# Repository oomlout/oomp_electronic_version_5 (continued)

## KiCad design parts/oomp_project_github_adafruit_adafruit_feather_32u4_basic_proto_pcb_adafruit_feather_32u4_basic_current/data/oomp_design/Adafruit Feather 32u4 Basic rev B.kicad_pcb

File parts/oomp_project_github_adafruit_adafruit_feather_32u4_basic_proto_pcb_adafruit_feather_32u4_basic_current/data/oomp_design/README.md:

# OOMP KiCad design copy

Open `Adafruit Feather 32u4 Basic rev B.kicad_pro` (or the `.kicad_pcb` / `.kicad_sch`) in KiCad. Local OOMP libraries are under `libraries/`. Original inputs are preserved in [../original/](../original/).

Only verified unchanged installed KiCad defaults were renamed. Modified, custom, unmatched and unavailable items remain unchanged. Soldering variants are never swapped during conversion. Existing pad coordinates, nets and UUIDs are preserved.

See [conversion_report.yaml](conversion_report.yaml) for every conversion and skip. Copy this directory before editing; regeneration refuses to overwrite edited design files.

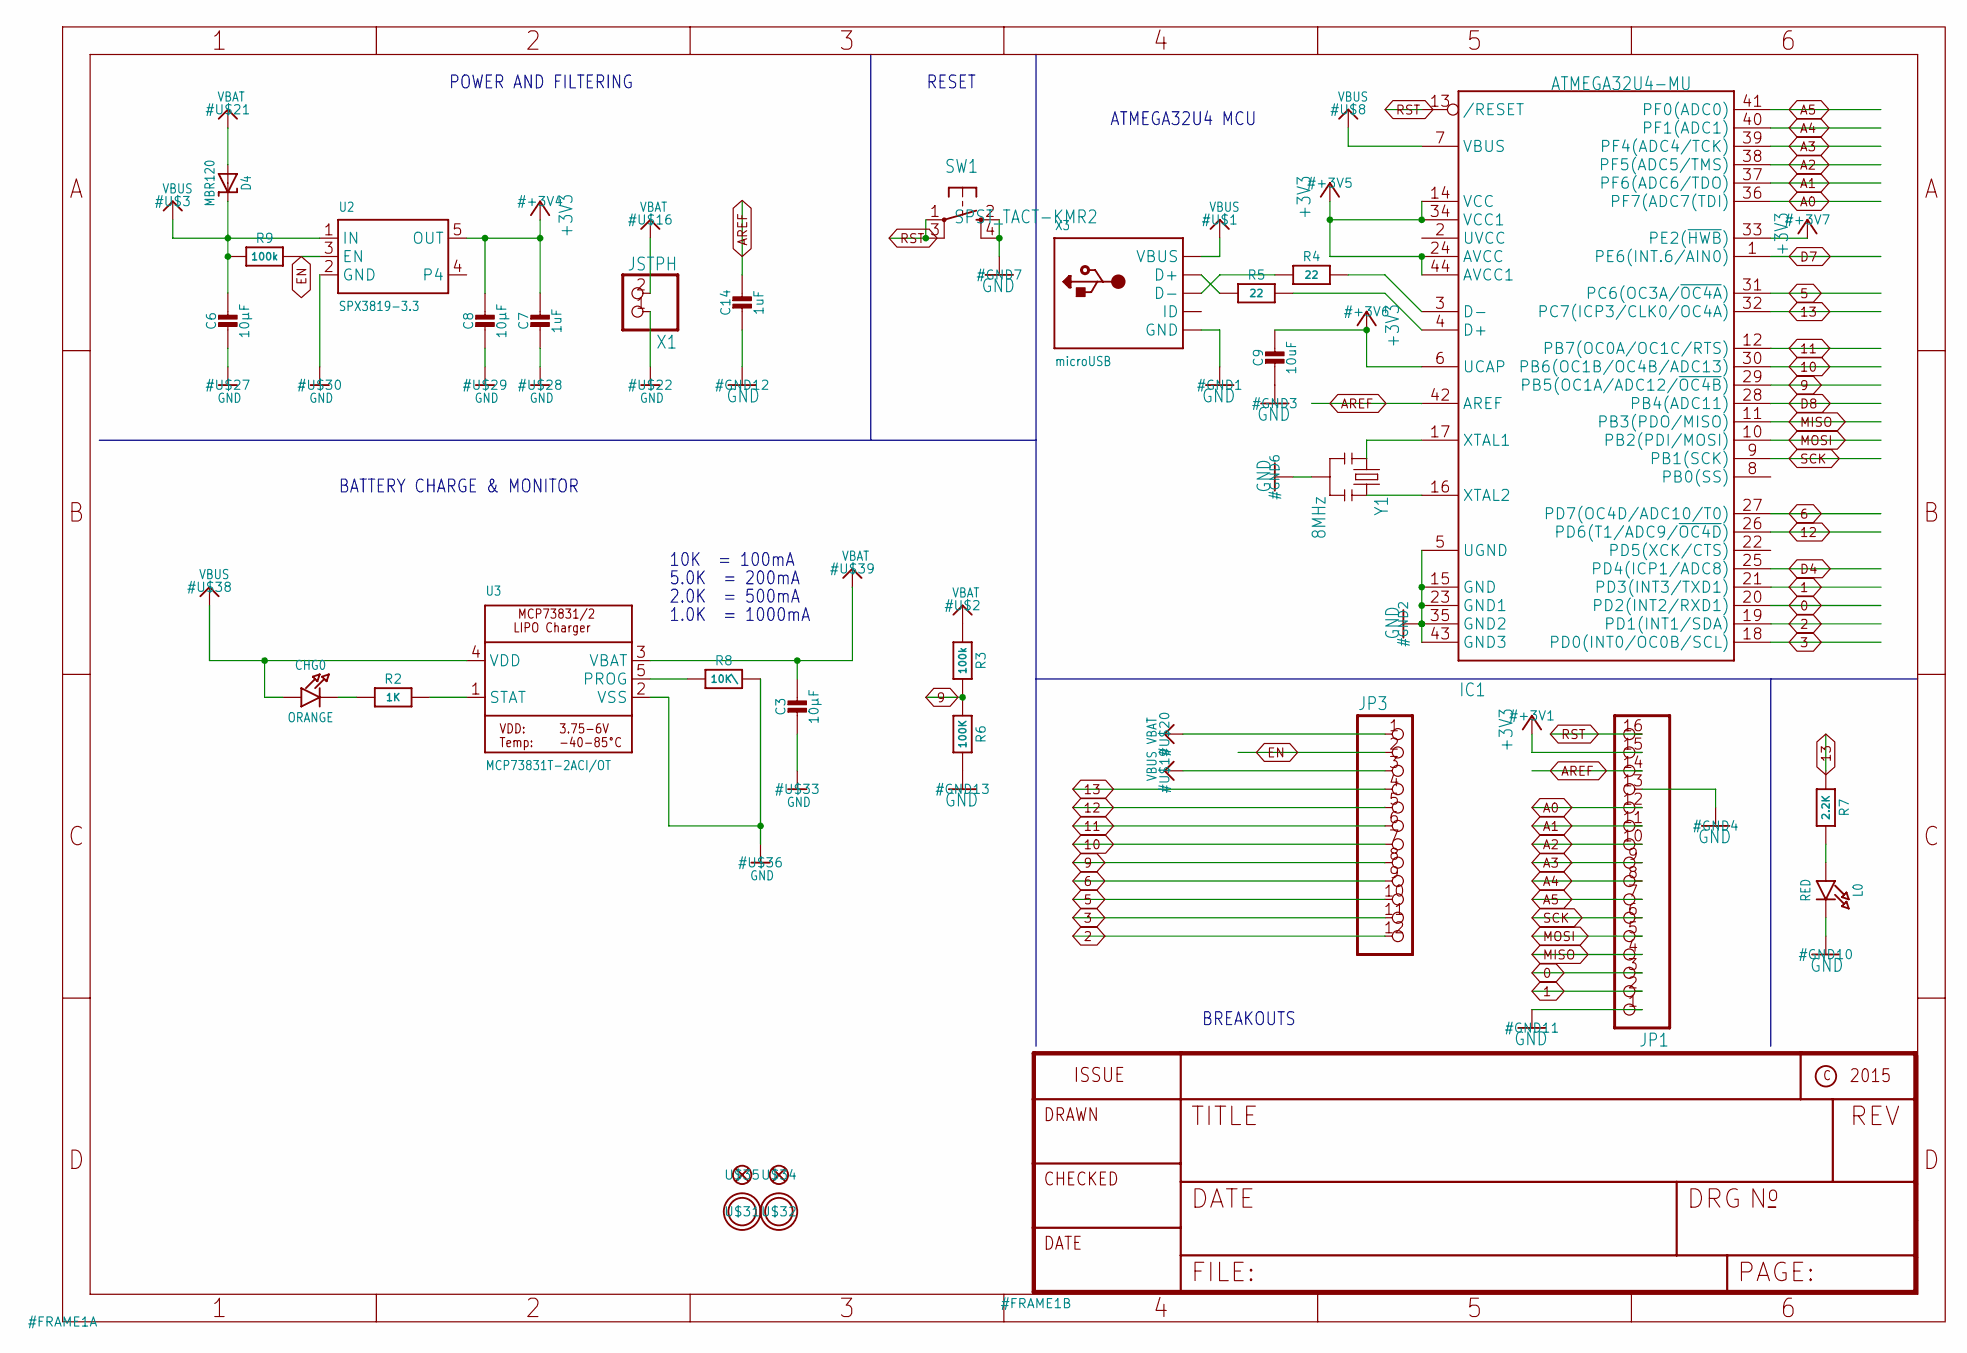
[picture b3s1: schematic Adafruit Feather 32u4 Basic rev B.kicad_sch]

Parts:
C3, C6, C8: 10µF; 0805-NO
C7, C14: 1uF; 0603-NO
C9: 10uF; 0805-NO
CHG0: ORANGE; CHIPLED_0805_NOOUTLINE
D4: MBR120; SOD-123
IC1: ATMEGA32U4-MU; TQFN44_7MM
JP1: HEADER-1X16ROUND; 1X16_ROUND
JP3: HEADER-1X12; 1X12_ROUND
L0: RED; CHIPLED_0805_NOOUTLINE
R2: 1K; 0603-NO
R3, R9: 100k; 0603-NO
R4, R5: 22; 0603-NO
R6: 100K; _0603MP
R7: 2.2K; 0603-NO
R8: 10K\; 0603-NO
SW1: SPST_TACT-KMR2; KMR2
U2: SPX3819-3.3; SOT23-5
U3: MCP73831T-2ACI/OT; SOT23-5
U$31, U$32: MOUNTINGHOLE2.5; MOUNTINGHOLE_2.5_PLATED
U$34, U$35: FIDUCIAL""; FIDUCIAL_1MM
X1: JSTPH; JSTPH2
X3: microUSB; 4UCONN_20329_V2
Y1: 8MHz; RESONATOR-SMD

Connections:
0: IC1.20 (PD2(INT2/RXD1)), JP1.3
1: IC1.21 (PD3(INT3/TXD1)), JP1.2
2: IC1.19 (PD1(INT1/SDA)), JP3.12
3: IC1.18 (PD0(INT0/OC0B/SCL)), JP3.11
5: IC1.31 (PC6(OC3A/~OC4A)), JP3.10
6: IC1.27 (PD7(OC4D/ADC10/T0)), JP3.9
9: IC1.29 (PB5(OC1A/ADC12/~OC4B)), JP3.8, R3.2, R6.1
10: IC1.30 (PB6(OC1B/OC4B/ADC13)), JP3.7
11: IC1.12 (PB7(OC0A/OC1C/RTS)), JP3.6
12: IC1.26 (PD6(T1/ADC9/~OC4D)), JP3.5
13: IC1.32 (PC7(ICP3/CLK0/OC4A)), JP3.4, R7.1
+3V3: C7.1, C8.1, C9.1, IC1.6 (UCAP), IC1.14 (VCC), IC1.24 (AVCC), IC1.33 (PE2(~HWB)), IC1.34 (VCC1), IC1.44 (AVCC1), JP1.15, U2.5 (OUT)
A0: IC1.36 (PF7(ADC7(TDI)), JP1.12
A1: IC1.37 (PF6(ADC6/TDO)), JP1.11
A2: IC1.38 (PF5(ADC5/TMS)), JP1.10
A3: IC1.39 (PF4(ADC4/TCK)), JP1.9
A4: IC1.40 (PF1(ADC1)), JP1.8
A5: IC1.41 (PF0(ADC0)), JP1.7
AREF: C14.1, IC1.42 (AREF), JP1.14
D4: IC1.25 (PD4(ICP1/ADC8))
D7: IC1.1 (PE6(INT.6/AIN0))
D8: IC1.28 (PB4(ADC11))
D+: IC1.4 (D+), R5.2
D-: IC1.3 (D-), R4.2
EN: JP3.2, R9.2, U2.3 (EN)
GND: C3.2, C6.2, C7.2, C8.2, C9.2, C14.2, IC1.5 (UGND), IC1.15 (GND), IC1.23 (GND1), IC1.35 (GND2), IC1.43 (GND3), JP1.1, JP1.13, L0.C, R6.2, R8.2, SW1.2 (S), SW1.4 (S1), U2.2 (GND), U3.2 (VSS), X1.1, X3.BASE@1 (GND), X3.BASE@2 (GND), X3.GND, X3.SPRT@1 (GND), X3.SPRT@2 (GND), X3.SPRT@3 (GND), X3.SPRT@4 (GND), Y1.2
MISO: IC1.11 (PB3(PDO/MISO)), JP1.4
MOSI: IC1.10 (PB2(PDI/MOSI)), JP1.5
unnamed: CHG0.C, R2.1
unnamed: L0.A, R7.2
unnamed: R2.2, U3.1 (STAT)
unnamed: R8.1, U3.5 (PROG)
unnamed: IC1.16 (XTAL2), Y1.3
unnamed: IC1.17 (XTAL1), Y1.1
unnamed: R5.1, X3.D+
unnamed: R4.1, X3.D-
RST: IC1.13 (/RESET), JP1.16, SW1.1, SW1.3 (P1)
SCK: IC1.9 (PB1(SCK)), JP1.6
VBAT: C3.1, D4.A, JP3.1, R3.1, U3.3 (VBAT), X1.2
VBUS: C6.1, CHG0.A, D4.C, IC1.7 (VBUS), JP3.3, R9.1, U2.1 (IN), U3.4 (VDD), X3.VBUS

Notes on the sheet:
POWER AND FILTERING
BATTERY CHARGE & MONITOR
5.0K = 200mA
2.0K = 500mA
RESET
BREAKOUTS
1.0K = 1000mA
10K = 100mA
ATMEGA32U4 MCU

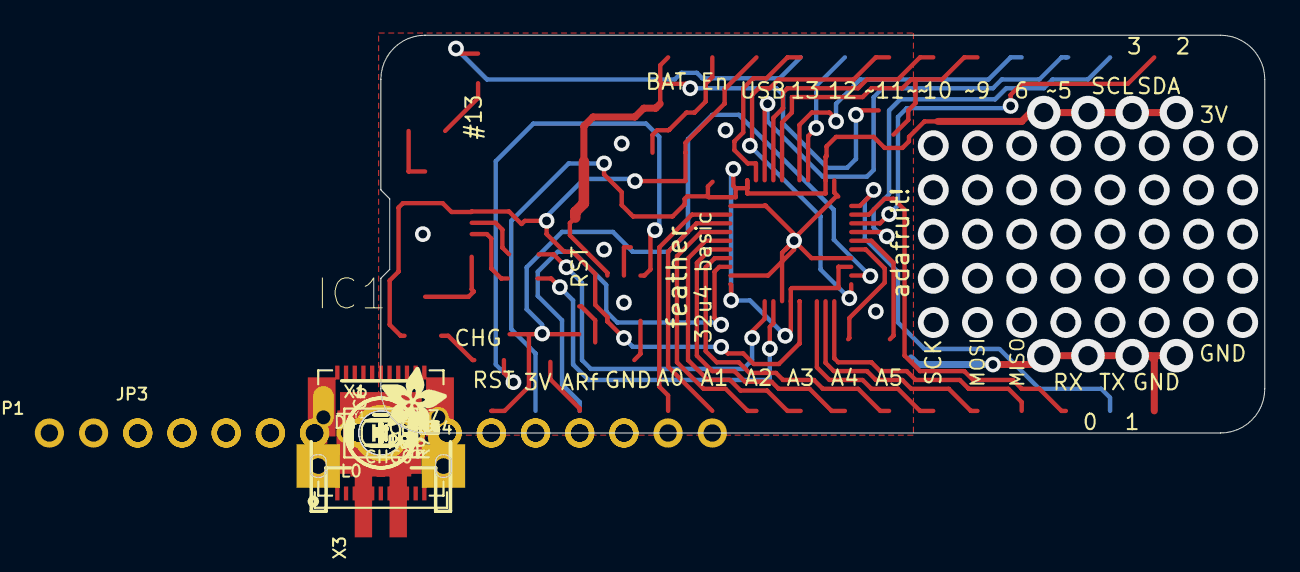
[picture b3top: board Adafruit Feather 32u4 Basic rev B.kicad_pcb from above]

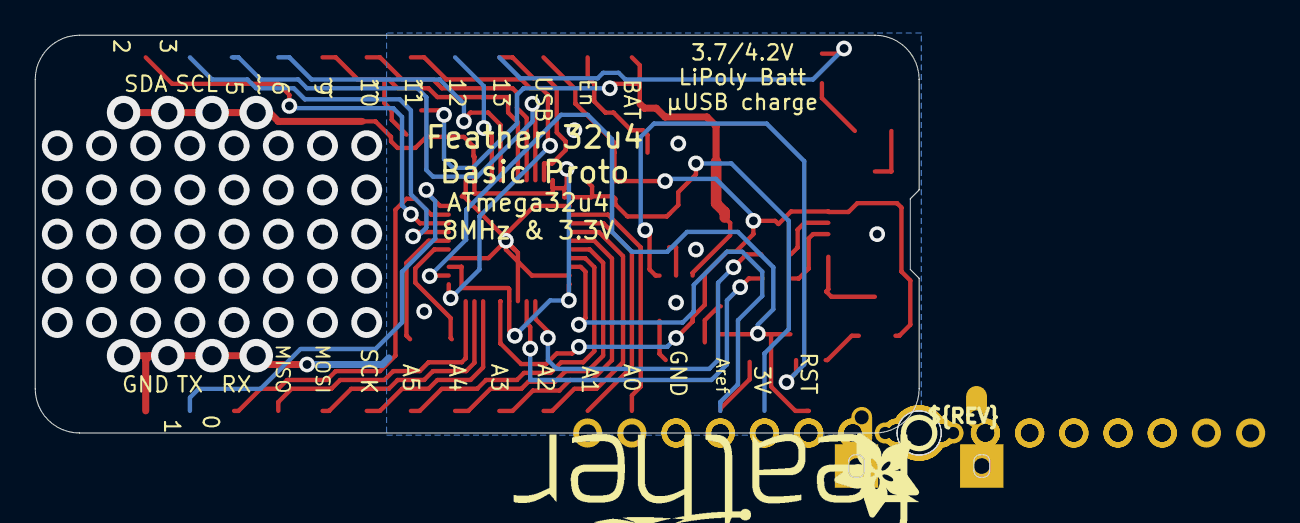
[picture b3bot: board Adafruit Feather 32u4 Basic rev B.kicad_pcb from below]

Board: 2 copper layers, 50.8 x 22.9 mm, 36 parts (3 on the bottom side), 37 nets.

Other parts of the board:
U$4: ADAFRUIT_5MM
U$5: FEATHERLOGO
U$6: PCBFEAT-REV-040
U$7: ADAFRUIT_3.5MM
UNK_HOLE_0: dummyfp0
UNK_HOLE_1: dummyfp1

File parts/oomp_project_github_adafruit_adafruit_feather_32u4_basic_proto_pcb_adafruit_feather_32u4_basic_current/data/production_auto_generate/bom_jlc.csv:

Comment,Designator,Footprint,LCSC Part #
,JP3,Adafruit Feather 32u4 Basic rev B-import-fps:1X12_ROUND,C7501588
,JP1,Adafruit Feather 32u4 Basic rev B-import-fps:1X16_ROUND,C7501270
,U$7,Adafruit Feather 32u4 Basic rev B-import-fps:ADAFRUIT_3.5MM,
,U$4,Adafruit Feather 32u4 Basic rev B-import-fps:ADAFRUIT_5MM,
,U$5,Adafruit Feather 32u4 Basic rev B-import-fps:FEATHERLOGO,
,U$6,Adafruit Feather 32u4 Basic rev B-import-fps:PCBFEAT-REV-040,
100k,"R3,R9",Adafruit Feather 32u4 Basic rev B-import-fps:0603-NO,C25803
100K,R6,Adafruit Feather 32u4 Basic rev B-import-fps:_0603MP,C25803
10K\,R8,Adafruit Feather 32u4 Basic rev B-import-fps:0603-NO,C98220
10uF,C9,Adafruit Feather 32u4 Basic rev B-import-fps:0805-NO,
10µF,"C3,C6,C8",Adafruit Feather 32u4 Basic rev B-import-fps:0805-NO,
1K,R2,Adafruit Feather 32u4 Basic rev B-import-fps:0603-NO,C2907002
1uF,"C7,C14",Adafruit Feather 32u4 Basic rev B-import-fps:0603-NO,C5673
2.2K,R7,Adafruit Feather 32u4 Basic rev B-import-fps:0603-NO,C4190
22,"R4,R5",Adafruit Feather 32u4 Basic rev B-import-fps:0603-NO,C23345
8MHz,Y1,Adafruit Feather 32u4 Basic rev B-import-fps:RESONATOR-SMD,
ATMEGA32U4-MU,IC1,Adafruit Feather 32u4 Basic rev B-import-fps:TQFN44_7MM,
"FIDUCIAL""""","U$34,U$35",Adafruit Feather 32u4 Basic rev B-import-fps:FIDUCIAL_1MM,
JSTPH,X1,Adafruit Feather 32u4 Basic rev B-import-fps:JSTPH2,
MBR120,D4,Adafruit Feather 32u4 Basic rev B-import-fps:SOD-123,
MCP73831T-2ACI/OT,U3,Adafruit Feather 32u4 Basic rev B-import-fps:SOT23-5,
microUSB,X3,Adafruit Feather 32u4 Basic rev B-import-fps:4UCONN_20329_V2,
ORANGE,CHG0,Adafruit Feather 32u4 Basic rev B-import-fps:CHIPLED_0805_NOOUTLINE,
RED,L0,Adafruit Feather 32u4 Basic rev B-import-fps:CHIPLED_0805_NOOUTLINE,
SPST_TACT-KMR2,SW1,Adafruit Feather 32u4 Basic rev B-import-fps:KMR2,
SPX3819-3.3,U2,Adafruit Feather 32u4 Basic rev B-import-fps:SOT23-5,
